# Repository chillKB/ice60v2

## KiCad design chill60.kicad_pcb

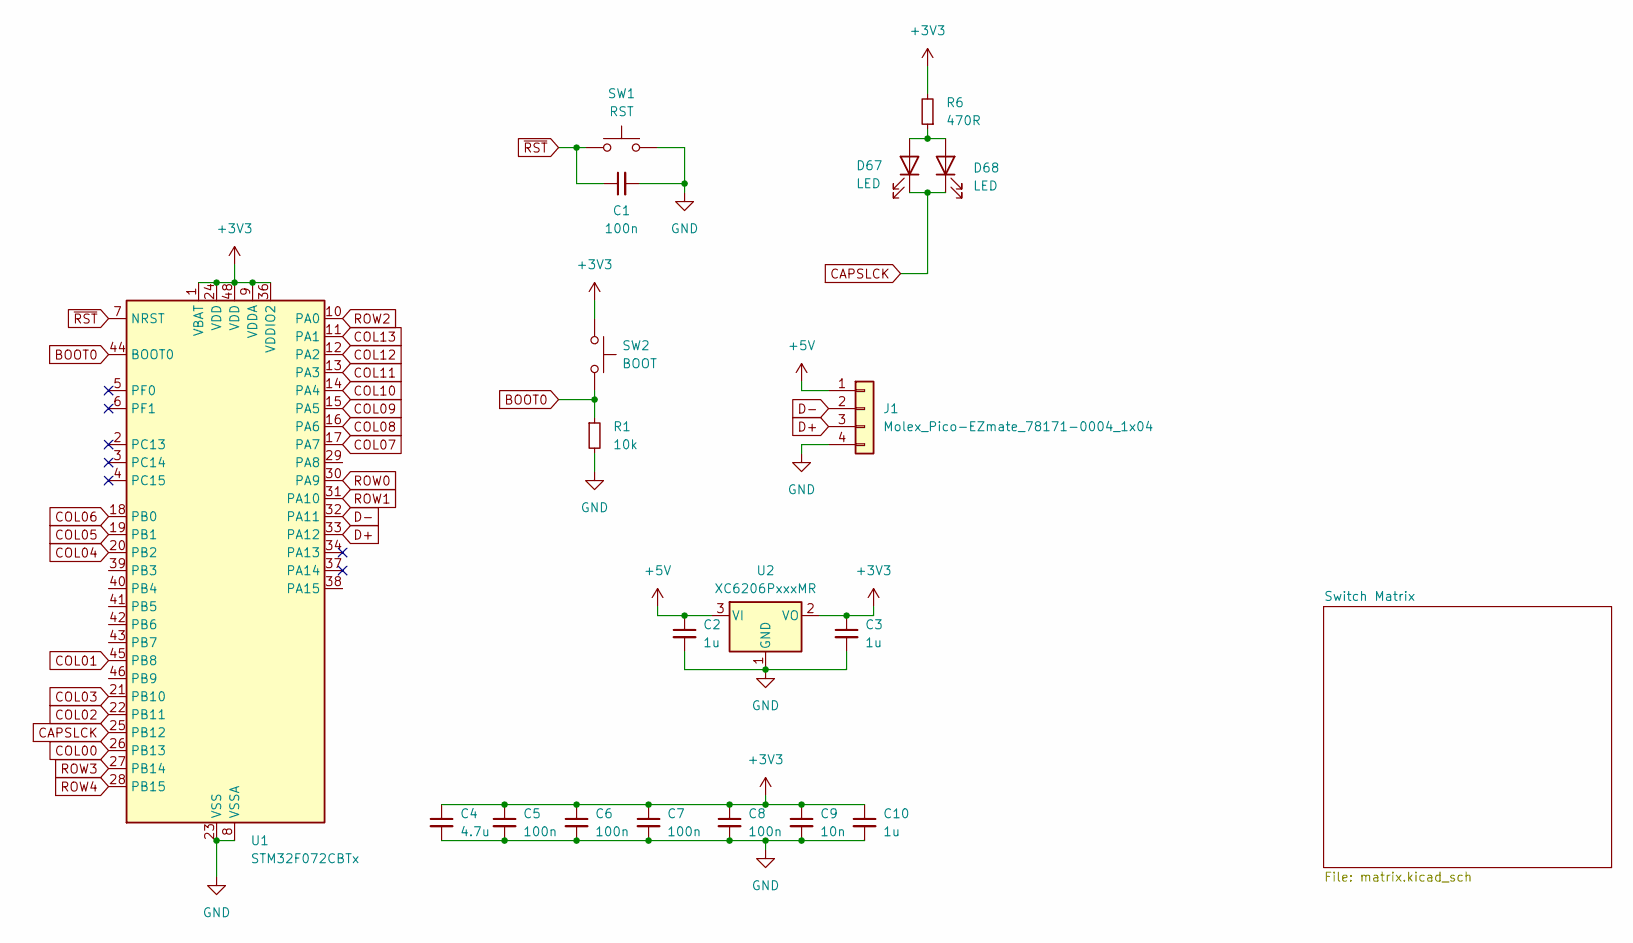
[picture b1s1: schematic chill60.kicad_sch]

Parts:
C1, C5, C6, C7, C8: 100n; C_0402_1005Metric
C2, C3, C10: 1u; C_0402_1005Metric
C4: 4.7u; C_0402_1005Metric
C9: 10n; C_0402_1005Metric
D67: LED; LED_MX_3mm
D68: LED; LED_MX_3mm-ROT
J1: Molex_Pico-EZmate_78171-0004_1x04; Molex_Pico-EZmate_78171-0004_1x04-1MP_P1.20mm_Vertical
R1: 10k; R_0603_1608Metric
R6: 470R; R_0402_1005Metric; LCSC C25117
SW1: RST; SW_SPST_TL3342
SW2: BOOT; SW_SPST_TL3342
U1: STM32F072CBTx; LQFP-48_7x7mm_P0.5mm
U2: XC6206PxxxMR; SOT-23-3

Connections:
+3V3: C3.1, C4.1, C5.1, C6.1, C7.1, C8.1, C9.1, C10.1, SW2.1, U1.1 (VBAT), U1.9 (VDDA), U1.24 (VDD), U1.36 (VDDIO2), U1.48 (VDD), U2.2 (VO); also elsewhere on the board
+5V: C2.1, J1.1, U2.3 (VI)
BOOT0: R1.1, SW2.2, U1.44 (BOOT0)
CAPSLCK: U1.25 (PB12); also elsewhere on the board
COL00: U1.26 (PB13); also elsewhere on the board
COL01: U1.45 (PB8); also elsewhere on the board
COL02: U1.22 (PB11); also elsewhere on the board
COL03: U1.21 (PB10); also elsewhere on the board
COL04: U1.20 (PB2); also elsewhere on the board
COL05: U1.19 (PB1); also elsewhere on the board
COL06: U1.18 (PB0); also elsewhere on the board
COL07: U1.17 (PA7); also elsewhere on the board
COL08: U1.16 (PA6); also elsewhere on the board
COL09: U1.15 (PA5); also elsewhere on the board
COL10: U1.14 (PA4); also elsewhere on the board
COL11: U1.13 (PA3); also elsewhere on the board
COL12: U1.12 (PA2); also elsewhere on the board
COL13: U1.11 (PA1); also elsewhere on the board
D+: J1.3, U1.33 (PA12)
D-: J1.2, U1.32 (PA11)
GND: C1.2, C2.2, C3.2, C4.2, C5.2, C6.2, C7.2, C8.2, C9.2, C10.2, J1.4, R1.2, SW1.2, U1.8 (VSSA), U1.23 (VSS), U1.35 (VSS), U1.47 (VSS), U2.1 (GND)
ROW0: U1.30 (PA9); also elsewhere on the board
ROW1: U1.31 (PA10); also elsewhere on the board
ROW2: U1.10 (PA0); also elsewhere on the board
ROW3: U1.27 (PB14); also elsewhere on the board
ROW4: U1.28 (PB15); also elsewhere on the board
~RST: C1.1, SW1.1, U1.7 (NRST)

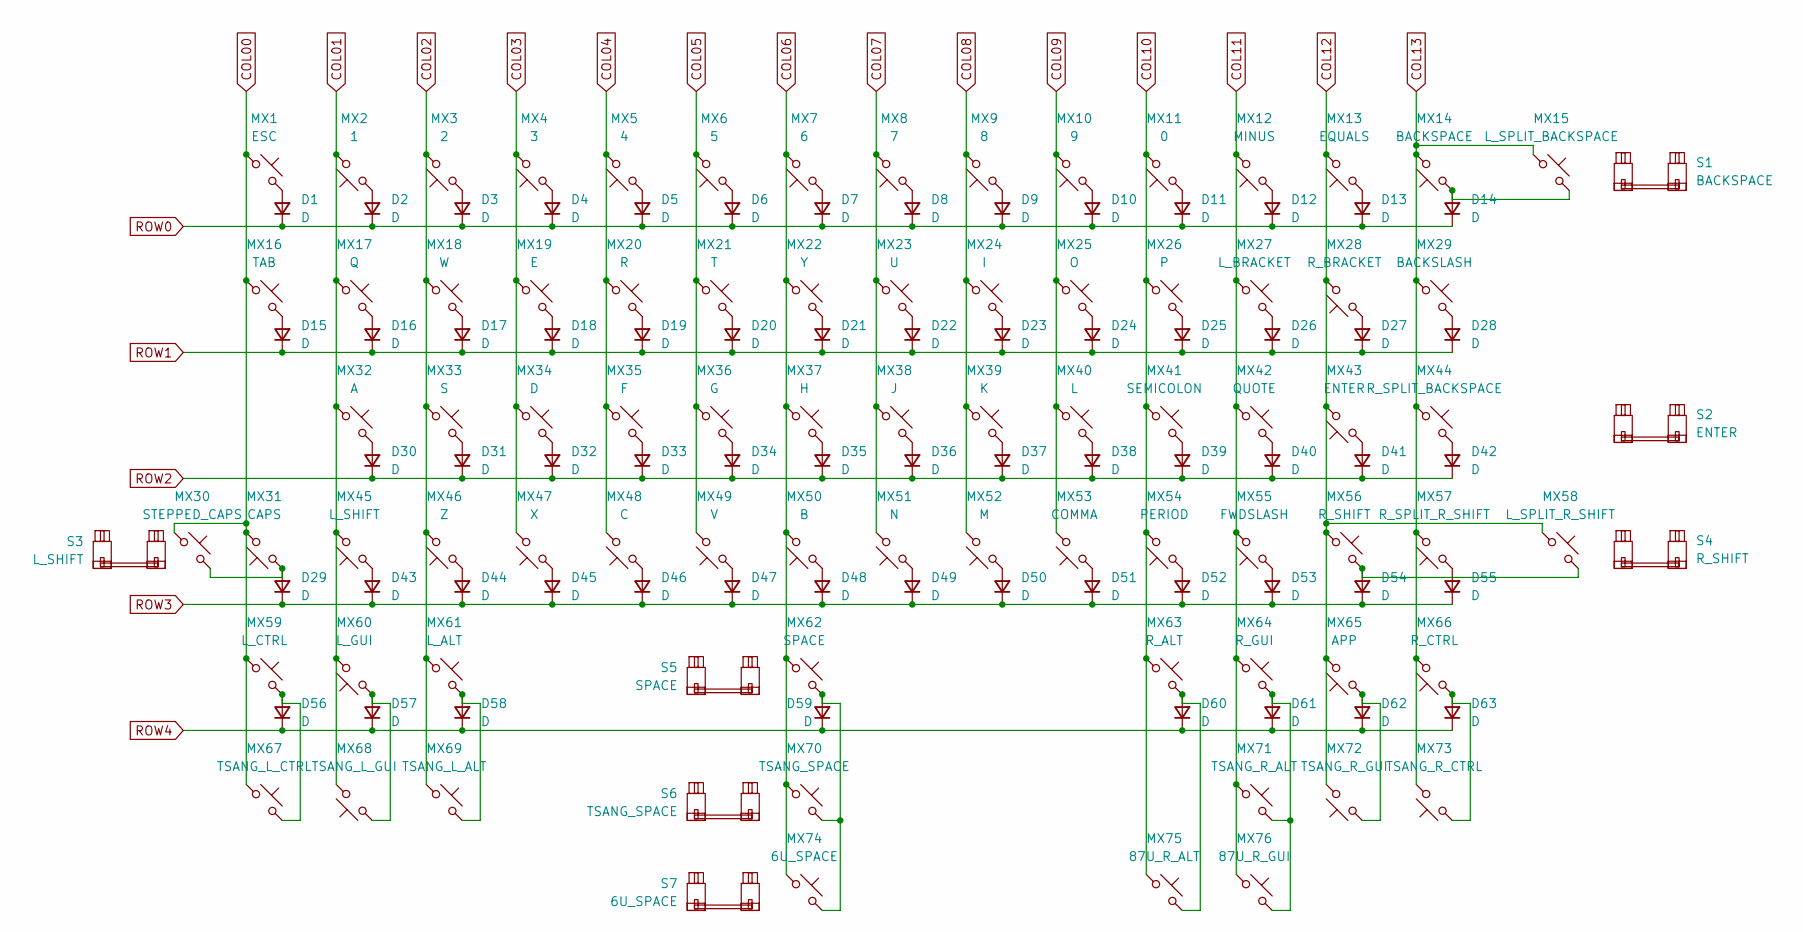
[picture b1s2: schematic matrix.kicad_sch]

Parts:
D1, D2, D3, D4, D5, D6, D7, D8, D9, D10, D11, D12, D13, D14, D15, D16, D17, D18, D19, D20, D21, D22, D23, D24, D25, D26, D27, D28, D29, D30, D31, D32, D33, D34, D35, D36, D37, D38, D39, D40, D41, D42, D43, D44, D45, D46, D47, D48, D49, D50, D51, D52, D53, D54, D55, D56, D57, D58, D59, D60, D61, D62, D63: D; D_SOD-123
MX1: ESC; SW_MX_1u
MX2: 1; SW_MX_1u
MX3: 2; SW_MX_1u
MX4: 3; SW_MX_1u
MX5: 4; SW_MX_1u
MX6: 5; SW_MX_1u
MX7: 6; SW_MX_1u
MX8: 7; SW_MX_1u
MX9: 8; SW_MX_1u
MX10: 9; SW_MX_1u
MX11: 0; SW_MX_1u
MX12: MINUS; SW_MX_1u
MX13: EQUALS; SW_MX_1u
MX14: BACKSPACE; SW_MX_1u
MX15: L_SPLIT_BACKSPACE; SW_MX_1u
MX16: TAB; SW_MX_1.5u
MX17: Q; SW_MX_1u
MX18: W; SW_MX_1u
MX19: E; SW_MX_1u
MX20: R; SW_MX_1u
MX21: T; SW_MX_1u
MX22: Y; SW_MX_1u
MX23: U; SW_MX_1u
MX24: I; SW_MX_1u
MX25: O; SW_MX_1u
MX26: P; SW_MX_1u
MX27: L_BRACKET; SW_MX_1u
MX28: R_BRACKET; SW_MX_1u
MX29: BACKSLASH; SW_MX_1.5u
MX30: STEPPED_CAPS; SW_MX_1.75u_STP_1.25
MX31: CAPS; SW_MX_1.75u
MX32: A; SW_MX_1u
MX33: S; SW_MX_1u
MX34: D; SW_MX_1u
MX35: F; SW_MX_1u
MX36: G; SW_MX_1u
MX37: H; SW_MX_1u
MX38: J; SW_MX_1u
MX39: K; SW_MX_1u
MX40: L; SW_MX_1u
MX41: SEMICOLON; SW_MX_1u
MX42: QUOTE; SW_MX_1u
MX43: ENTER; SW_MX_1u
MX44: R_SPLIT_BACKSPACE; SW_MX_1u
MX45: L_SHIFT; SW_MX_1u
MX46: Z; SW_MX_1u
MX47: X; SW_MX_1u
MX48: C; SW_MX_1u
MX49: V; SW_MX_1u
MX50: B; SW_MX_1u
MX51: N; SW_MX_1u
MX52: M; SW_MX_1u
MX53: COMMA; SW_MX_1u
MX54: PERIOD; SW_MX_1u
MX55: FWDSLASH; SW_MX_1u
MX56: R_SHIFT; SW_MX_1u
MX57: R_SPLIT_R_SHIFT; SW_MX_1u
MX58: L_SPLIT_R_SHIFT; SW_MX_1.75u
MX59: L_CTRL; SW_MX_1.25u
MX60: L_GUI; SW_MX_1.25u
MX61: L_ALT; SW_MX_1.25u
MX62: SPACE; SW_MX_1u
MX63: R_ALT; SW_MX_1.25u
MX64: R_GUI; SW_MX_1.25u
MX65: APP; SW_MX_1.25u
MX66: R_CTRL; SW_MX_1.25u
MX67: TSANG_L_CTRL; SW_MX_1.5u
MX68: TSANG_L_GUI; SW_MX_1u
MX69: TSANG_L_ALT; SW_MX_1.5u
MX70: TSANG_SPACE; SW_MX_1u
MX71: TSANG_R_ALT; SW_MX_1.5u
MX72: TSANG_R_GUI; SW_MX_1u
MX73: TSANG_R_CTRL; SW_MX_1.5u
MX74: 6U_SPACE; SW_MX_1u
MX75: 87U_R_ALT; SW_MX_1.5u
MX76: 87U_R_GUI; SW_MX_1u
S1: BACKSPACE; STAB_MX_2u
S2: ENTER; STAB_MX_2.25u
S3: L_SHIFT; STAB_MX_2.25u
S4: R_SHIFT; STAB_MX_2.75u
S5: SPACE; STAB_MX_6.25u
S6: TSANG_SPACE; STAB_MX_7u
S7: 6U_SPACE; STAB_MX_6u

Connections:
COL00: MX1.1, MX16.1, MX30.1, MX31.2, MX59.1, MX67.1; also elsewhere on the board
COL01: MX2.2, MX17.1, MX32.1, MX45.2, MX60.2, MX68.2; also elsewhere on the board
COL02: MX3.2, MX18.1, MX33.1, MX46.2, MX61.1, MX69.1; also elsewhere on the board
COL03: MX4.2, MX19.1, MX34.1, MX47.2; also elsewhere on the board
COL04: MX5.2, MX20.1, MX35.1, MX48.2; also elsewhere on the board
COL05: MX6.2, MX21.1, MX36.1, MX49.2; also elsewhere on the board
COL06: MX7.2, MX22.1, MX37.1, MX50.2, MX62.1, MX70.1, MX74.1; also elsewhere on the board
COL07: MX8.2, MX23.1, MX38.1, MX51.2; also elsewhere on the board
COL08: MX9.2, MX24.1, MX39.1, MX52.2; also elsewhere on the board
COL09: MX10.2, MX25.1, MX40.1, MX53.2; also elsewhere on the board
COL10: MX11.2, MX26.1, MX41.1, MX54.2, MX63.1, MX75.1; also elsewhere on the board
COL11: MX12.2, MX27.1, MX42.1, MX55.2, MX64.1, MX71.1, MX76.1; also elsewhere on the board
COL12: MX13.2, MX28.2, MX43.2, MX56.1, MX58.1, MX65.2, MX72.2; also elsewhere on the board
COL13: MX14.2, MX15.1, MX29.1, MX44.1, MX57.2, MX66.2, MX73.2; also elsewhere on the board
unnamed: D1.2 (A), MX1.2
unnamed: D2.2 (A), MX2.1
unnamed: D3.2 (A), MX3.1
unnamed: D4.2 (A), MX4.1
unnamed: D5.2 (A), MX5.1
unnamed: D6.2 (A), MX6.1
unnamed: D7.2 (A), MX7.1
unnamed: D8.2 (A), MX8.1
unnamed: D9.2 (A), MX9.1
unnamed: D10.2 (A), MX10.1
unnamed: D11.2 (A), MX11.1
unnamed: D12.2 (A), MX12.1
unnamed: D13.2 (A), MX13.1
unnamed: D14.2 (A), MX14.1, MX15.2
unnamed: D15.2 (A), MX16.2
unnamed: D16.2 (A), MX17.2
unnamed: D17.2 (A), MX18.2
unnamed: D18.2 (A), MX19.2
unnamed: D19.2 (A), MX20.2
unnamed: D20.2 (A), MX21.2
unnamed: D21.2 (A), MX22.2
unnamed: D22.2 (A), MX23.2
unnamed: D23.2 (A), MX24.2
unnamed: D24.2 (A), MX25.2
unnamed: D25.2 (A), MX26.2
unnamed: D26.2 (A), MX27.2
unnamed: D27.2 (A), MX28.1
unnamed: D28.2 (A), MX29.2
unnamed: D29.2 (A), MX30.2, MX31.1
unnamed: D30.2 (A), MX32.2
unnamed: D31.2 (A), MX33.2
unnamed: D32.2 (A), MX34.2
unnamed: D33.2 (A), MX35.2
unnamed: D34.2 (A), MX36.2
unnamed: D35.2 (A), MX37.2
unnamed: D36.2 (A), MX38.2
unnamed: D37.2 (A), MX39.2
unnamed: D38.2 (A), MX40.2
unnamed: D39.2 (A), MX41.2
unnamed: D40.2 (A), MX42.2
unnamed: D41.2 (A), MX43.1
unnamed: D42.2 (A), MX44.2
unnamed: D43.2 (A), MX45.1
unnamed: D44.2 (A), MX46.1
unnamed: D45.2 (A), MX47.1
unnamed: D46.2 (A), MX48.1
unnamed: D47.2 (A), MX49.1
unnamed: D48.2 (A), MX50.1
unnamed: D49.2 (A), MX51.1
unnamed: D50.2 (A), MX52.1
unnamed: D51.2 (A), MX53.1
unnamed: D52.2 (A), MX54.1
unnamed: D53.2 (A), MX55.1
unnamed: D54.2 (A), MX56.2, MX58.2
unnamed: D55.2 (A), MX57.1
unnamed: D56.2 (A), MX59.2, MX67.2
unnamed: D57.2 (A), MX60.1, MX68.1
unnamed: D58.2 (A), MX61.2, MX69.2
unnamed: D59.2 (A), MX62.2, MX70.2, MX74.2
unnamed: D60.2 (A), MX63.2, MX75.2
unnamed: D61.2 (A), MX64.2, MX71.2, MX76.2
unnamed: D62.2 (A), MX65.1, MX72.1
unnamed: D63.2 (A), MX66.1, MX73.1
ROW0: D1.1 (K), D2.1 (K), D3.1 (K), D4.1 (K), D5.1 (K), D6.1 (K), D7.1 (K), D8.1 (K), D9.1 (K), D10.1 (K), D11.1 (K), D12.1 (K), D13.1 (K), D14.1 (K); also elsewhere on the board
ROW1: D15.1 (K), D16.1 (K), D17.1 (K), D18.1 (K), D19.1 (K), D20.1 (K), D21.1 (K), D22.1 (K), D23.1 (K), D24.1 (K), D25.1 (K), D26.1 (K), D27.1 (K), D28.1 (K); also elsewhere on the board
ROW2: D30.1 (K), D31.1 (K), D32.1 (K), D33.1 (K), D34.1 (K), D35.1 (K), D36.1 (K), D37.1 (K), D38.1 (K), D39.1 (K), D40.1 (K), D41.1 (K), D42.1 (K); also elsewhere on the board
ROW3: D29.1 (K), D43.1 (K), D44.1 (K), D45.1 (K), D46.1 (K), D47.1 (K), D48.1 (K), D49.1 (K), D50.1 (K), D51.1 (K), D52.1 (K), D53.1 (K), D54.1 (K), D55.1 (K); also elsewhere on the board
ROW4: D56.1 (K), D57.1 (K), D58.1 (K), D59.1 (K), D60.1 (K), D61.1 (K), D62.1 (K), D63.1 (K); also elsewhere on the board

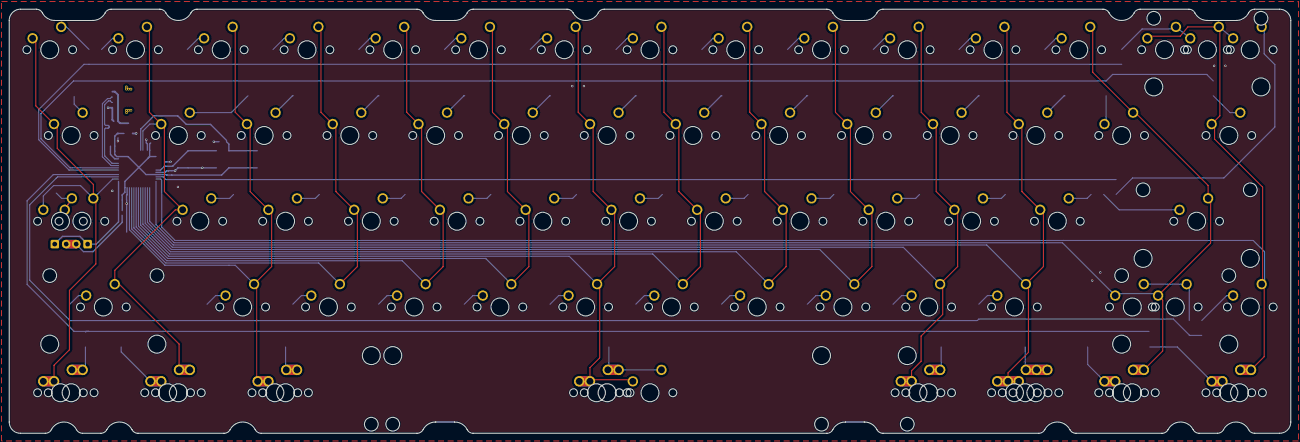
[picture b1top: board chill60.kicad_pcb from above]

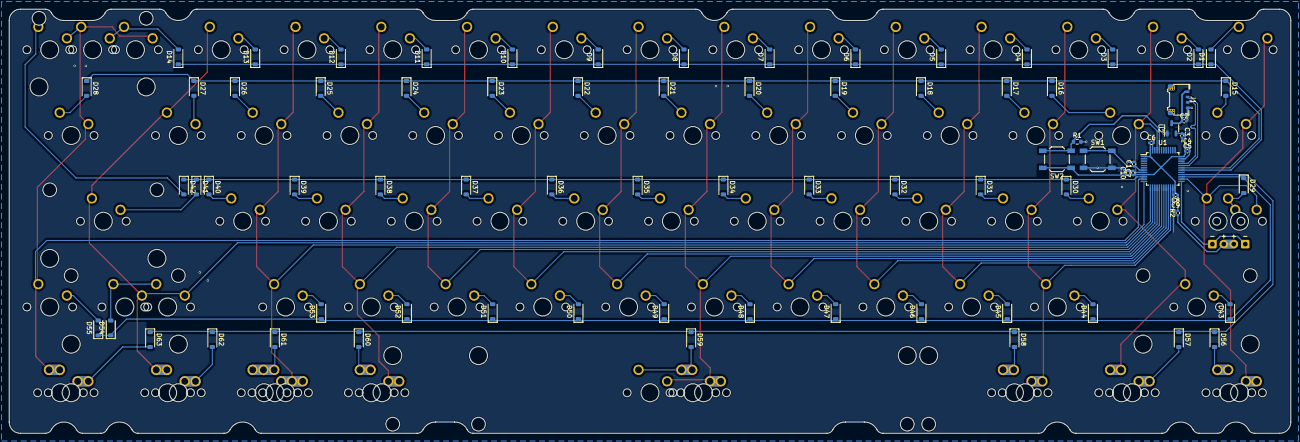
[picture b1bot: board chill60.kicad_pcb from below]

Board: 2 copper layers, 284.7 x 94.2 mm, 164 parts (80 on the bottom side), 91 nets.

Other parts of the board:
LED1: LED; LED_MX_3mm
LED2: LED; LED_MX_3mm-ROT
R2: 470R; R_0402_1005Metric

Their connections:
+3V3: R2.2; also elsewhere on the board
CAPSLCK: LED1.1 (K), LED2.1 (K); also elsewhere on the board
unnamed: LED1.2 (A), LED2.2 (A), R2.1

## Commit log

2023-07-10 create project
2023-07-10 add marbastlib
2023-07-10 actually add marbastlib
2023-07-10 update gitignore
2023-07-10 add basic components
2023-07-10 add switch diode matrix
2023-07-11 initial complete schematic
2023-07-11 remove USB terminating resistors (not needed)
2023-07-31 add PCB
2023-09-29 License under CERN-OHL-P
2023-09-29 rename files to ice60v2
2023-09-29 update to reflect new file names
2023-09-29 remove xyz60 support
